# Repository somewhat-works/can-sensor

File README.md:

# Can sensor
Can based sensor board has temperature, humidity, pressure, CO2.  
20V input  
I2C on board  
CAN off board  
Using uno r4 as usb to can adapter  

## To do:  
1. Get PCB  
2. Write code  
3. Test it
4. USBCOM from R4 adapter to SQL code  
5. Redo R4 part with stm32H5 for USB to CAN adapter and change to used full CAN FD

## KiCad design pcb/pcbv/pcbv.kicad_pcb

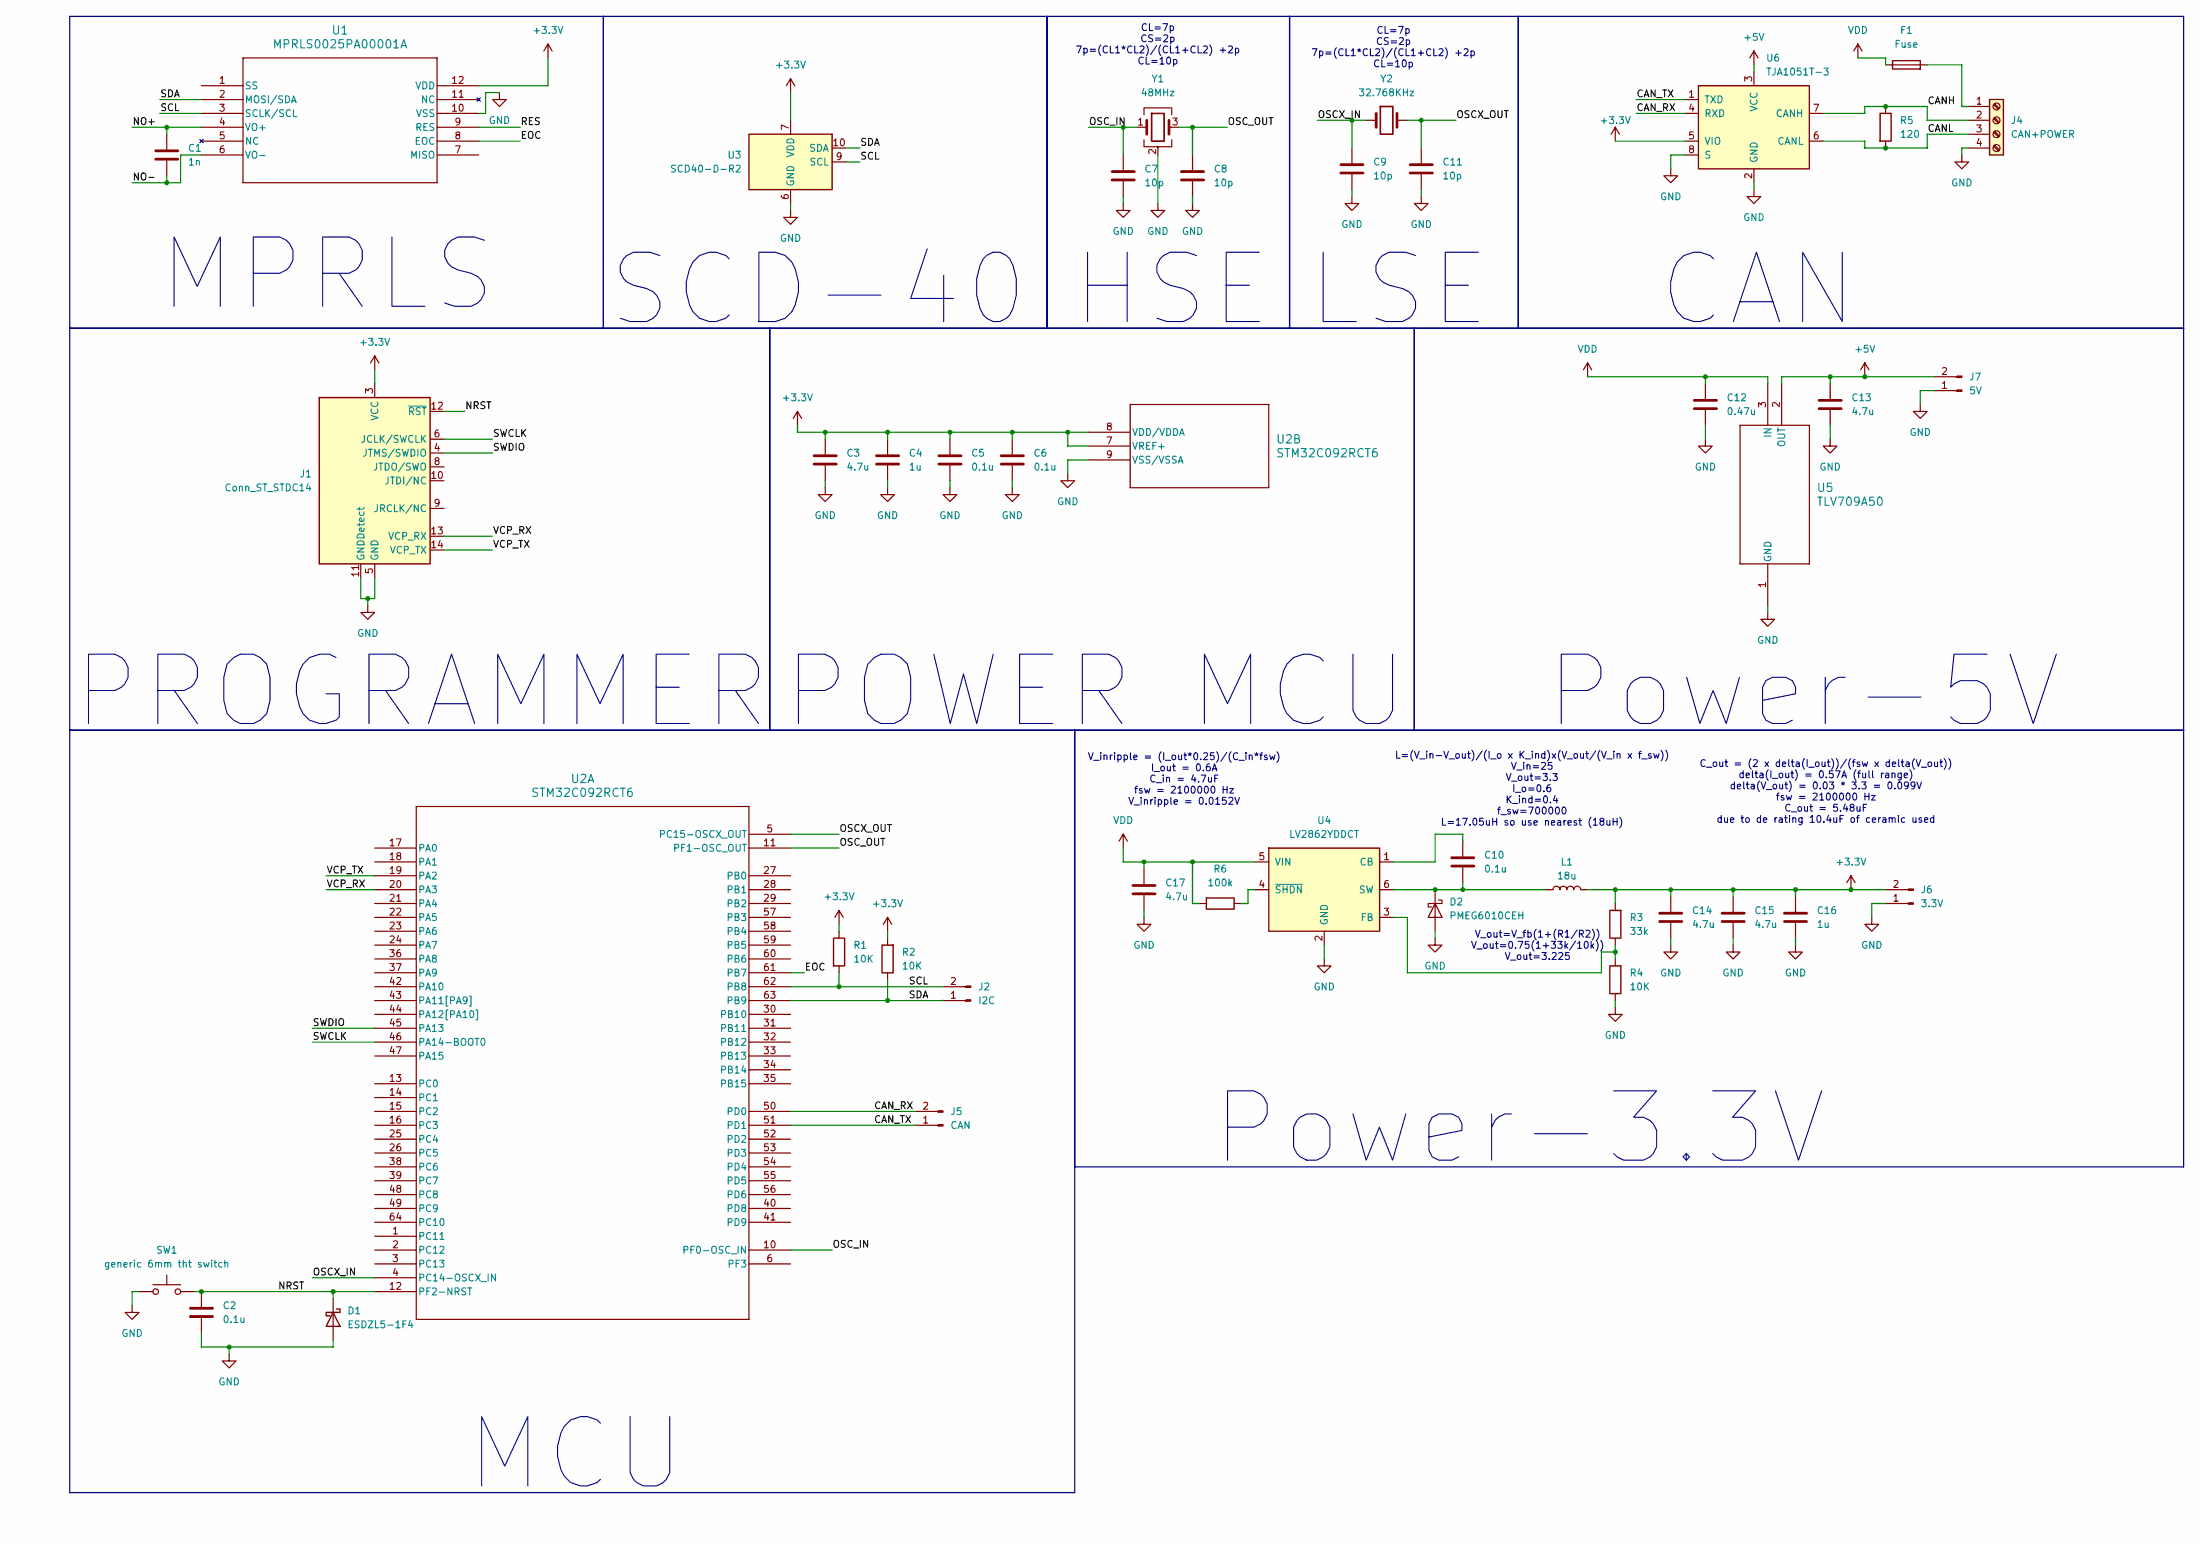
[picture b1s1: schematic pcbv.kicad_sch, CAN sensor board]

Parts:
C1: 1n; C_0805_2012Metric
C2, C5, C6, C10: 0.1u; C_1210_3225Metric
C3, C13, C14, C15, C17: 4.7u; C_1210_3225Metric
C4, C16: 1u; C_1210_3225Metric
C7, C8, C9, C11: 10p; C_0805_2012Metric
C12: 0.47u; C_1210_3225Metric
D1: ESDZL5-1F4; D_0201_0603Metric
D2: PMEG6010CEH; D_SOD-123F
F1: Fuse; Fuseholder_Clip-5x20mm_Bel_FC-203-22_Lateral_P17.80x5.00mm_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
J1: Conn_ST_STDC14; PinHeader_2x07_P1.27mm_Vertical
J2: I2C; PinHeader_1x02_P2.54mm_Vertical
J4: CAN+POWER; TerminalBlock_Phoenix_MKDS-1,5-4-5.08_1x04_P5.08mm_Horizont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
J5: CAN; PinHeader_1x02_P2.54mm_Vertical
J6: 3.3V; PinHeader_1x02_P2.54mm_Vertical
J7: 5V; PinHeader_1x02_P2.54mm_Vertical
L1: 18u; L_Taiyo-Yuden_MD-5050
R1, R2, R4: 10K; R_0805_2012Metric
R3: 33k; R_0805_2012Metric
R5: 120; R_0805_2012Metric
R6: 100k; R_0805_2012Metric
SW1: generic 6mm tht switch; SW_PUSH_6mm
U1: MPRLS0025PA00001A; MPRLS_HNW
U2: STM32C092RCT6; LQFP64_STM
U3: SCD40-D-R2; Sensirion_SCD4x-1EP_10.1x10.1mm_P1.25mm_EP4.8x4.8mm
U4: LV2862YDDCT; SOT-23-6
U5: TLV709A50; SOT-23_2p92X2p37_TLV1709_DBZ_TEX
U6: TJA1051T-3; SOIC-8_3.9x4.9mm_P1.27mm
Y1: 48MHz; Crystal_SMD_2016-4Pin_2.0x1.6mm
Y2: 32.768KHz; Crystal_SMD_MicroCrystal_CC7V-T1A-2Pin_3.2x1.5mm

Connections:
+3.3V: C3.1, C4.1, C5.1, C6.1, C14.1, C15.1, C16.1, J1.3 (VCC), J6.2, L1.2, R1.1, R2.2, R3.2, U1.12 (VDD), U2.7 (VREF+), U2.8 (VDD/VDDA), U3.7 (VDD), U3.19 (VDD), U6.5 (VIO)
+5V: C13.1, J7.2, U5.2 (OUT), U6.3 (VCC)
/CANH: J4.2, R5.1, U6.7 (CANH)
/CANL: J4.3, R5.2, U6.6 (CANL)
/CAN_RX: J5.2, U2.50 (PD0), U6.4 (RXD)
/CAN_TX: J5.1, U2.51 (PD1), U6.1 (TXD)
/EOC: U1.8 (EOC), U2.61 (PB7)
/NO+: C1.1, U1.4 (VO+)
/NO-: C1.2, U1.6 (VO-)
/NRST: C2.1, D1.1 (K), J1.12 (~RST), SW1.2, U2.12 (PF2-NRST)
/OSCX_IN: C9.1, U2.4 (PC14-OSCX_IN), Y2.1
/OSCX_OUT: C11.1, U2.5 (PC15-OSCX_OUT), Y2.2
/OSC_IN: C7.1, U2.10 (PF0-OSC_IN), Y1.1
/OSC_OUT: C8.1, U2.11 (PF1-OSC_OUT), Y1.3
/RES: U1.9 (RES)
/SCL: J2.2, R1.2, U1.3 (SCLK/SCL), U2.62 (PB8), U3.9 (SCL)
/SDA: J2.1, R2.1, U1.2 (MOSI/SDA), U2.63 (PB9), U3.10 (SDA)
/SWCLK: J1.6 (JCLK/SWCLK), U2.46 (PA14-BOOT0)
/SWDIO: J1.4 (JTMS/SWDIO), U2.45 (PA13)
/VCP_RX: J1.13 (VCP_RX), U2.20 (PA3)
/VCP_TX: J1.14 (VCP_TX), U2.19 (PA2)
GND: C2.2, C3.2, C4.2, C5.2, C6.2, C7.2, C8.2, C9.2, C11.2, C12.2, C13.2, C14.2, C15.2, C16.2, C17.2, D1.2 (A), D2.2 (A), J1.5 (GND), J1.7 (GND), J1.11 (GNDDetect), J4.4, J6.1, J7.1, R4.1, SW1.1, U1.10 (VSS), U2.9 (VSS/VSSA), U3.6 (GND), U3.20 (GND), U3.21 (GND), U4.2 (GND), U5.1 (GND), U6.2 (GND), U6.8 (S), Y1.2 (G), Y1.4 (G)
unnamed: C10.2, D2.1 (K), L1.1, U4.6 (SW)
unnamed: F1.2, J4.1
unnamed: C10.1, U4.1 (CB)
unnamed: R3.1, R4.2, U4.3 (FB)
unnamed: R6.1, U4.4 (~SHDN)
VDD: C12.1, C17.1, F1.1, R6.2, U4.5 (VIN), U5.3 (IN)

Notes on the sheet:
MCU
CL=7p CS=2p 7p=(CL1*CL2)/(CL1+CL2) +2p CL=10p
HSE
Power-5V
V_out=V_fb(1+(R1/R2)) V_out=0.75(1+33k/10k)) V_out=3.225
L=(V_in-V_out)/(I_o x K_ind)x(V_out/(V_in x f_sw)) V_in=25 V_out=3.3 I_o=0.6 K_ind=0.4 f_sw=700000 L=17.05uH so use nearest (18uH)
LSE
SCD-40
C_out = (2 x delta(I_out))/(fsw x delta(V_out)) delta(I_out) = 0.57A (full range) delta(V_out) = 0.03 * 3.3 = 0.099V fsw = 2100000 Hz C_out = 5.48uF due to de rating 10.4uF of ceramic used
PROGRAMMER
CAN
MPRLS
POWER MCU
Power-3.3V
V_inripple = (I_out*0.25)/(C_in*fsw) I_out = 0.6A C_in = 4.7uF fsw = 2100000 Hz V_inripple = 0.0152V

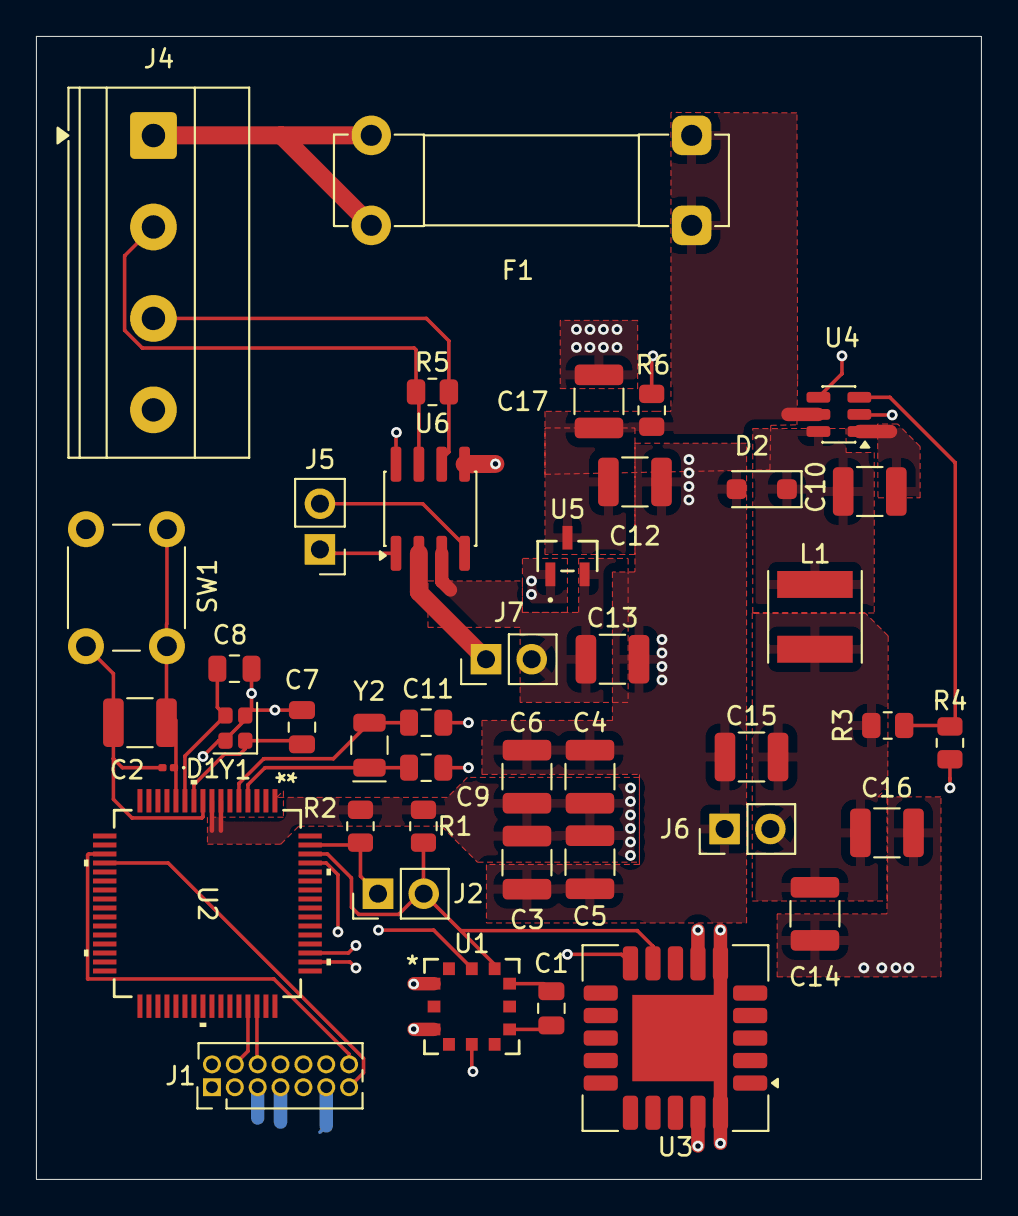
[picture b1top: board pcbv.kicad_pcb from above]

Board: 4 copper layers, 52.5 x 63.5 mm, 42 parts (0 on the bottom side), 27 nets.

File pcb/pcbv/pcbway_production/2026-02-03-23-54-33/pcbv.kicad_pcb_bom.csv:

Designator,Quantity,Value,Footprint,Package,MPN,DNP,Mount_Type,Description
C1,1,1n,C_0805_2012Metric,,,,smt,Unpolarized capacitor
"C10, C2, C5, C6",4,0.1u,C_1210_3225Metric,,,,smt,Unpolarized capacitor
"C11, C7, C8, C9",4,10p,C_0805_2012Metric,,,,smt,Unpolarized capacitor
C12,1,0.47u,C_1210_3225Metric,,,,smt,Unpolarized capacitor
"C13, C14, C15, C17, C3",5,4.7u,C_1210_3225Metric,,,,smt,Unpolarized capacitor
"C16, C4",2,1u,C_1210_3225Metric,,,,smt,Unpolarized capacitor
D1,1,ESDZL5,D_0201_0603Metric,,,,smt,Schottky diode
D2,1,PMEG6010CEH,D_SOD-123F,,,,smt,"60V, 1A very low Vf MEGA Schottky barrier rectifier, SOD-123F"
J1,1,Conn_ST_STDC14,PinHeader_2x07_P1.27mm_Vertical,,,,tht,"ST Debug Connector, standard ARM Cortex-M SWD and JTAG interface plus UART"
J2,1,I2C,PinHeader_1x02_P2.54mm_Vertical,,,,tht,"Generic connector, single row, 01x02, script generated"
J4,1,CAN+POWER,"TerminalBlock_Phoenix_MKDS-1,5-4-5.08_1x04_P5.08mm_Horizontal",,,,tht,"Generic screw terminal, single row, 01x04, script generated (kicad-library-utils/schlib/autogen/connector/)"
J5,1,CAN,PinHeader_1x02_P2.54mm_Vertical,,,,tht,"Generic connector, single row, 01x02, script generated"
J6,1,3.3V,PinHeader_1x02_P2.54mm_Vertical,,,,tht,"Generic connector, single row, 01x02, script generated"
J7,1,5V,PinHeader_1x02_P2.54mm_Vertical,,,,tht,"Generic connector, single row, 01x02, script generated"
L1,1,18u-RLB0914-180KL,L_Radial_D8.7mm_P5.00mm_Fastron_07HCP,,,,tht,Inductor
"R1, R2, R4",3,10K,R_0805_2012Metric,,,,smt,Resistor
R3,1,33k,R_0805_2012Metric,,,,smt,Resistor
R5,1,120,R_0805_2012Metric,,,,smt,Resistor
R6,1,100k,R_0805_2012Metric,,,,smt,Resistor
SW1,1,generic 6mm tht switch,SW_PUSH_6mm,,,,tht,"Push button switch, generic, two pins"
U1,1,MPRLS0025PA00001A,MPRLS_HNW,,,,smt,
U2,1,STM32C092RCT6,LQFP64_STM,,,,smt,
U3,1,SCD40-D-R2,Sensirion_SCD4x-1EP_10.1x10.1mm_P1.25mm_EP4.8x4.8mm,,,,smt,"Photoacoustic CO2 sensor, 40 000 ppm, I2C, 2.4-5.5 V, Base accuracy  400 - 2000 ppm"
U4,1,LV2862YDDC,SOT-23-6,,,,smt,"60V, 0.6A, stepdown, DC/DC converter, 2.1MHz"
U5,1,TLV709A50DBZR,SOT-23_2p92X2p37_TLV1709_DBZ_TEX,,,,smt,
U6,1,TJA1051T-3,SOIC-8_3.9x4.9mm_P1.27mm,,,,smt,"High-Speed CAN Transceiver, separate VIO, silent mode, SOIC-8"
Y1,1,48MHz,Crystal_SMD_2016-4Pin_2.0x1.6mm,,,,smt,"Four pin crystal, GND on pins 2 and 4"
Y2,1,32.768KHz,Crystal_SMD_MicroCrystal_CC7V-T1A-2Pin_3.2x1.5mm,,,,smt,Two pin crystal

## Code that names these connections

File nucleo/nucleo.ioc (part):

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Mcu.Name=STM32C092RCTx
Mcu.Package=LQFP64
Mcu.UserName=STM32C092RCTx
PA13.GPIOParameters=GPIO_Label
PA13.GPIO_Label=SWDIO
PA13.Signal=DEBUG_SWDIO
PA14-BOOT0.GPIOParameters=GPIO_Label
PA14-BOOT0.GPIO_Label=SWCLK
PA14-BOOT0.Signal=DEBUG_SWCLK
PA2.Signal=USART2_TX
PA3.Signal=USART2_RX
PA5.Signal=GPIO_Output
PB8.Mode=I2C
PB8.Signal=I2C1_SCL
PB9.Mode=I2C
PB9.Signal=I2C1_SDA
PC13.Signal=GPIO_Input
PC14-OSCX_IN(PC14).GPIOParameters=GPIO_Label
PC14-OSCX_IN(PC14).GPIO_Label=OSCX_IN
PC14-OSCX_IN(PC14).Signal=RCC_OSCX_IN
PC15-OSCX_OUT(PC15).GPIOParameters=GPIO_Label
PC15-OSCX_OUT(PC15).GPIO_Label=OSCX_OUT
PC15-OSCX_OUT(PC15).Signal=RCC_OSCX_OUT
PD0.Mode=FDCAN_Activate
PD0.Signal=FDCAN1_RX
PD1.Mode=FDCAN_Activate
PD1.Signal=FDCAN1_TX
PF0-OSC_IN(PF0).GPIOParameters=GPIO_Label
PF0-OSC_IN(PF0).GPIO_Label=OSC_IN
PF0-OSC_IN(PF0).Signal=RCC_OSC_IN
PF1-OSC_OUT(PF1).GPIOParameters=GPIO_Label
PF1-OSC_OUT(PF1).GPIO_Label=OSC_OUT
PF1-OSC_OUT(PF1).Signal=RCC_OSC_OUT
RCC.HSE_VALUE=8000000
RCC.SYSCLKFreq_VALUE=48000000
board=NUCLEO-C092RC
boardIOC=true

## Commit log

2026-01-30 initial
2026-01-30 Add section about home use can sensor
2026-01-30 Add PolyForm Noncommercial License 1.0.0
    Added the PolyForm Noncommercial License 1.0.0 to the project.
2026-02-02 initial pcb rev
2026-02-02 Update README with sensor details
2026-02-02 Update README with sensor board details
2026-02-02 Fix formatting of 'To do' section in README
2026-02-02 Update README formatting and section headers
2026-02-02 Fix punctuation in README description
2026-02-08 pcb updated
